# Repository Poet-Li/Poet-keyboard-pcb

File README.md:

# Poet keyboard pcb
 base on ai03-pcb-guide

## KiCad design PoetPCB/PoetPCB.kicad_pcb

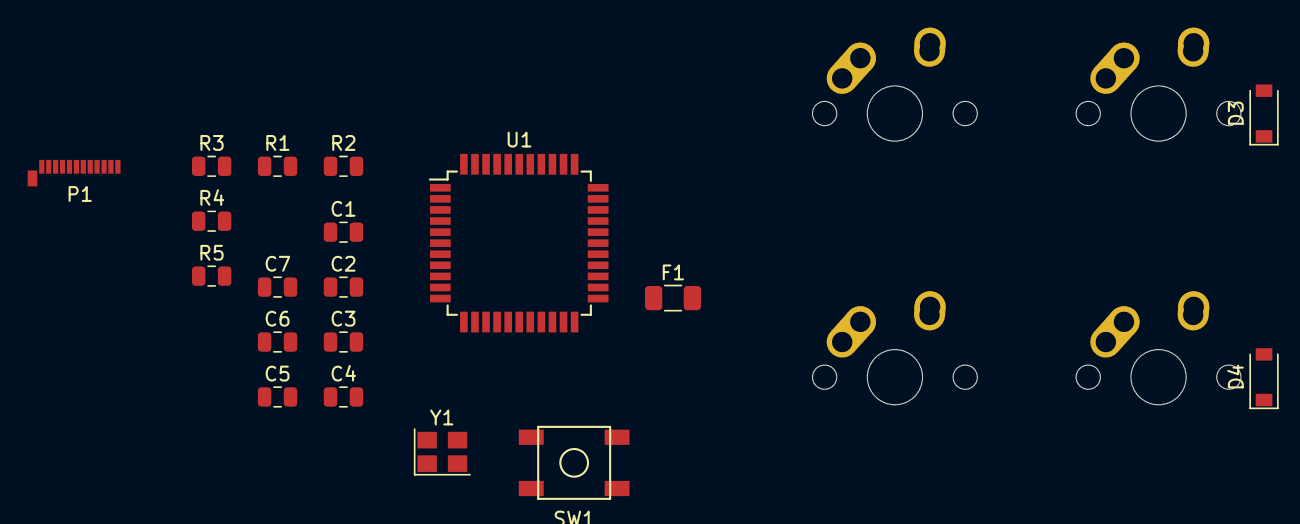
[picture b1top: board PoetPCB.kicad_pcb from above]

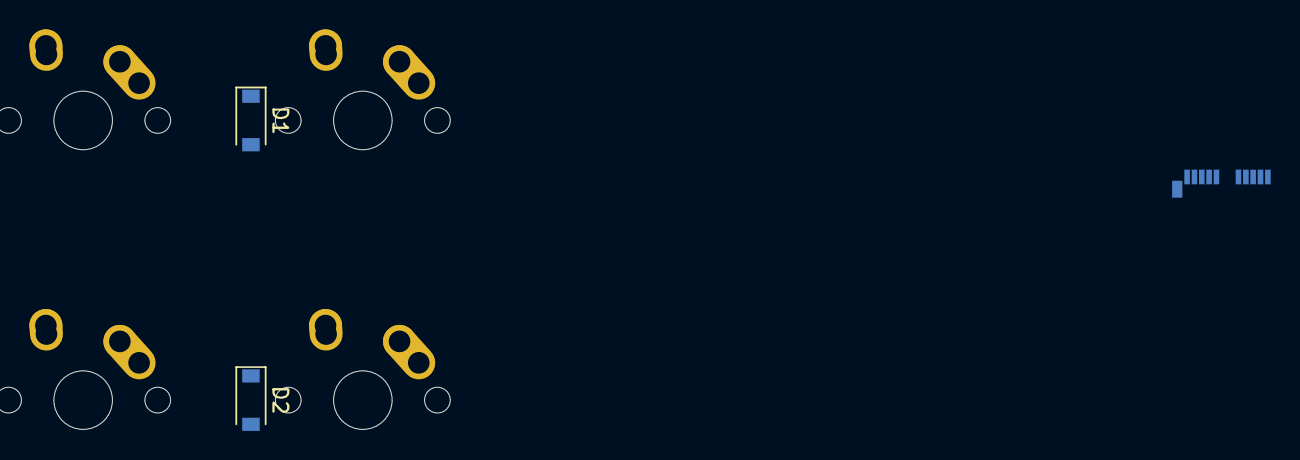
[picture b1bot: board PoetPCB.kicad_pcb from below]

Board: 2 copper layers, 25 parts (2 on the bottom side), 21 nets, no tracks yet.

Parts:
C1, C2, C5: 0.1uF; C_0805_2012Metric
C3, C4: 22pF; C_0805_2012Metric
C6: 10uF; C_0805_2012Metric
C7: 1uF; C_0805_2012Metric
D1, D2, D3, D4: D_Small; D_SOD-123
F1: 500mA; Fuse_1206_3216Metric
MX1, MX2, MX3, MX4: MX-NoLED; MX-1U-NoLED
P1: USB_C_Plug; USB_C_Plug_Molex_105444
R1, R2: 22; R_0805_2012Metric
R3, R4, R5: 10k; R_0805_2012Metric
SW1: SW_Push; SKQG-1155865
U1: ATmega32U4-AU; TQFP-44_10x10mm_P0.8mm
Y1: Crystal_GND24_Small; Crystal_SMD_3225-4Pin_3.2x2.5mm

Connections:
+5V: C1.1, C2.1, C5.1, C6.1, F1.1, R3.1, U1.2, U1.7, U1.14, U1.24, U1.34, U1.44
COL0: MX1.1, MX2.1
COL1: MX3.1, MX4.1
D+: P1.A6, R2.2
D-: P1.A7, R1.2
GND: C1.2, C2.2, C3.2, C4.2, C5.2, C6.2, C7.2, P1.A1, P1.A12, P1.B1, P1.B12, P1.S1, R4.1, R5.1, SW1.1, U1.5, U1.15, U1.23, U1.35, U1.43, Y1.2, Y1.4
unnamed: C3.1, U1.17, Y1.1
unnamed: C4.1, U1.16, Y1.3
unnamed: C7.1, U1.6
unnamed: D1.2, MX1.2
unnamed: D2.2, MX2.2
unnamed: D3.2, MX3.2
unnamed: D4.2, MX4.2
unnamed: P1.A5, R5.2
unnamed: R1.1, U1.3
unnamed: R2.1, U1.4
unnamed: R3.2, SW1.2, U1.13
unnamed: R4.2, U1.33
ROW0: D1.1, D3.1, U1.27, U1.28
ROW1: D2.1, D4.1, U1.29, U1.30
VCC: F1.2, P1.A4, P1.A9, P1.B4, P1.B9

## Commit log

2020-12-17 Create project
2020-12-17 Add submodules
2020-12-17 Add footprint lib
2020-12-17 Add type-C
2020-12-17 Add type-C lib
